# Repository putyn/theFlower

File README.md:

the flower
=========

leds, low power msp430, custom pcb shape, oshpark purple & ENIG

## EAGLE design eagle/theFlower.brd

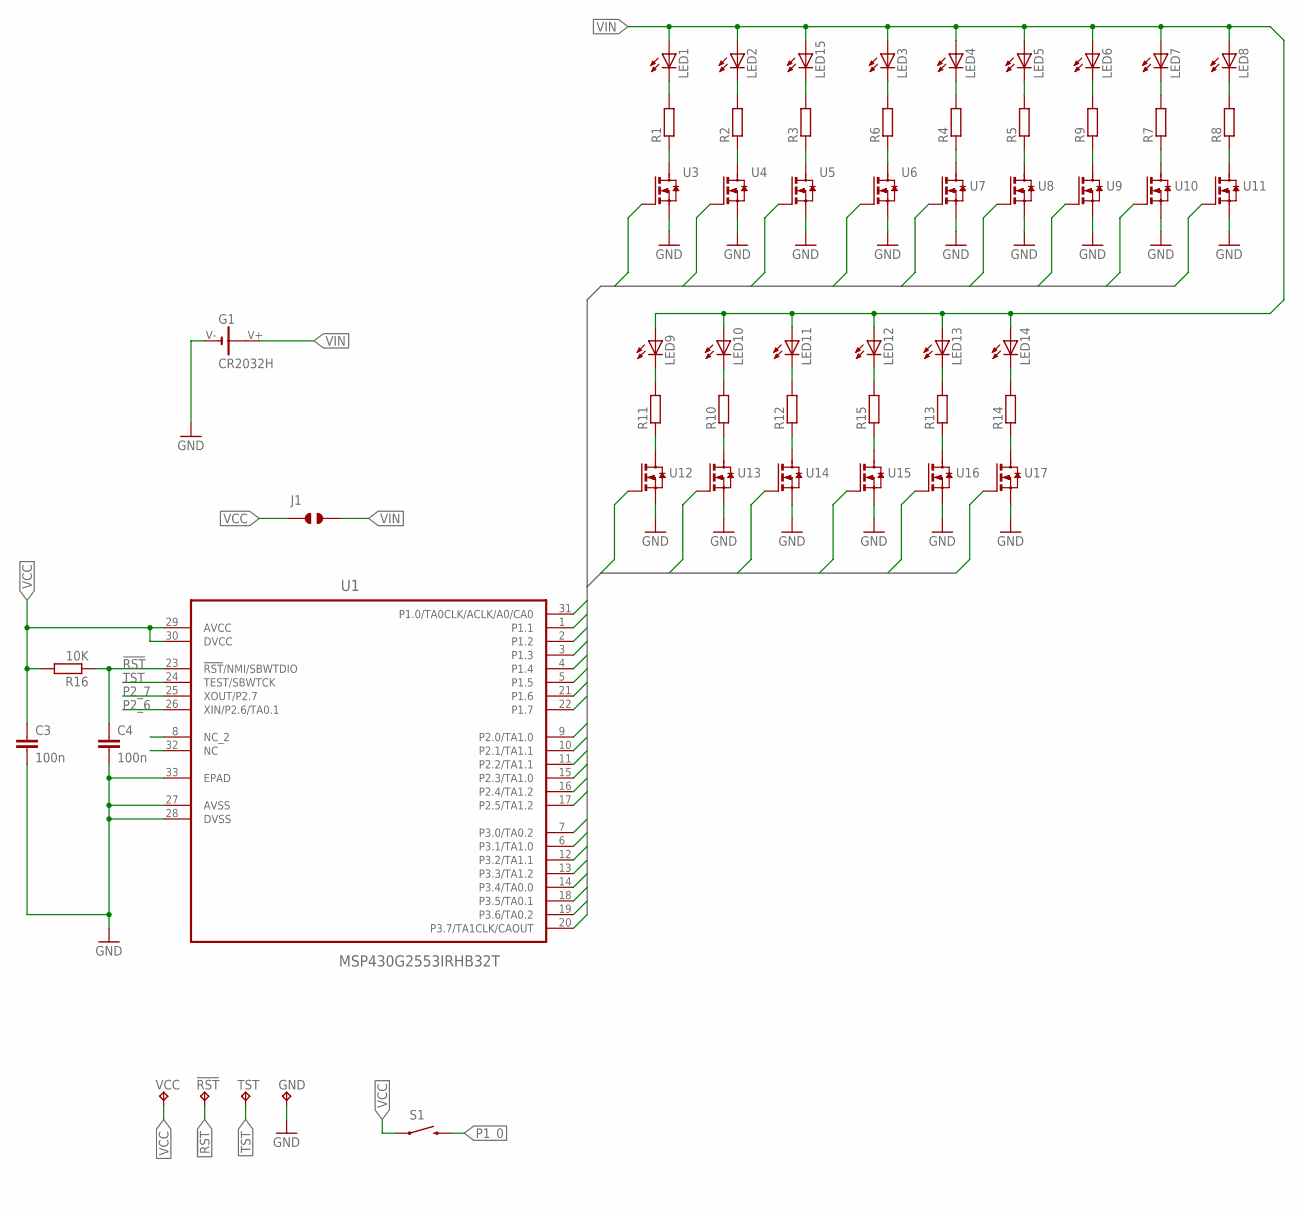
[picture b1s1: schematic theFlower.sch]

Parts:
!RST!: TPAD0.8MM_RUND; TPAD_0.8MM_RUND
C3, C4: 100n; C0603
G1: CR2032H; CH7410-2032LF
GND: TPAD0.8MM_RUND; TPAD_0.8MM_RUND
J1: JUMPER_SOLDER_1X2
LED1, LED2, LED3, LED4, LED5, LED6, LED7, LED8, LED9, LED10, LED11, LED12, LED13, LED14, LED15: LEDCHIP-LED0805; CHIP-LED0805
R1, R2, R3, R4, R5, R6, R7, R8, R9, R10, R11, R12, R13, R14, R15: R-EU_R0603; R0603
R16: 10K; R0603
S1: SWITCH-MOMENTARY-2SMD; TACTILE-SWITCH-SMD
TST: TPAD0.8MM_RUND; TPAD_0.8MM_RUND
U1: MSP430G2553IRHB32T; QFN50P500X500X100-33N
U3, U4, U5, U6, U7, U8, U9, U10, U11, U12, U13, U14, U15, U16, U17: BSS138BKW; SOT65P210X110-3N
VCC: TPAD0.8MM_RUND; TPAD_0.8MM_RUND

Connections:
!RST!: !RST!.1, C4.1, R16.1, U1.23 (!RST!/NMI/SBWTDIO)
GND: C3.2, C4.2, G1.V-, GND.1, U1.27 (AVSS), U1.28 (DVSS), U1.33 (EPAD), U3.2 (S), U4.2 (S), U5.2 (S), U6.2 (S), U7.2 (S), U8.2 (S), U9.2 (S), U10.2 (S), U11.2 (S), U12.2 (S), U13.2 (S), U14.2 (S), U15.2 (S), U16.2 (S), U17.2 (S)
unnamed: LED1.C, R1.2
unnamed: LED2.C, R2.2
unnamed: LED15.C, R3.2
unnamed: LED4.C, R4.2
unnamed: LED5.C, R5.2
unnamed: LED3.C, R6.2
unnamed: LED7.C, R7.2
unnamed: LED8.C, R8.2
unnamed: LED6.C, R9.2
unnamed: LED10.C, R10.2
unnamed: LED9.C, R11.2
unnamed: LED11.C, R12.2
unnamed: LED13.C, R13.2
unnamed: LED14.C, R14.2
unnamed: LED12.C, R15.2
unnamed: R1.1, U3.3 (D)
unnamed: R2.1, U4.3 (D)
unnamed: R3.1, U5.3 (D)
unnamed: R6.1, U6.3 (D)
unnamed: R4.1, U7.3 (D)
unnamed: R5.1, U8.3 (D)
unnamed: R9.1, U9.3 (D)
unnamed: R7.1, U10.3 (D)
unnamed: R8.1, U11.3 (D)
unnamed: R11.1, U12.3 (D)
unnamed: R10.1, U13.3 (D)
unnamed: R12.1, U14.3 (D)
unnamed: R15.1, U15.3 (D)
unnamed: R13.1, U16.3 (D)
unnamed: R14.1, U17.3 (D)
NC: U1.32 (NC)
NC_2: U1.8 (NC_2)
P1_0: S1.3 (2), U1.31 (P1.0/TA0CLK/ACLK/A0/CA0)
P1_1: U1.1 (P1.1), U5.1 (G)
P1_2: U1.2 (P1.2), U3.1 (G)
P1_3: U1.3 (P1.3), U4.1 (G)
P1_4: U1.4 (P1.4), U6.1 (G)
P1_5: U1.5 (P1.5), U7.1 (G)
P1_6: U1.21 (P1.6), U16.1 (G)
P1_7: U1.22 (P1.7), U17.1 (G)
P2_0: U1.9 (P2.0/TA1.0), U10.1 (G)
P2_1: U1.10 (P2.1/TA1.1), U11.1 (G)
P2_2: U1.11 (P2.2/TA1.1), U12.1 (G)
P2_3: U1.15 (P2.3/TA1.0)
P2_4: U1.16 (P2.4/TA1.2)
P2_5: U1.17 (P2.5/TA1.2)
P2_6: U1.26 (XIN/P2.6/TA0.1)
P2_7: U1.25 (XOUT/P2.7)
P3_0: U1.7 (P3.0/TA0.2), U9.1 (G)
P3_1: U1.6 (P3.1/TA1.0), U8.1 (G)
P3_2: U1.12 (P3.2/TA1.1), U13.1 (G)
P3_3: U1.13 (P3.3/TA1.2), U14.1 (G)
P3_4: U1.14 (P3.4/TA0.0)
P3_5: U1.18 (P3.5/TA0.1)
P3_6: U1.19 (P3.6/TA0.2)
P3_7: U1.20 (P3.7/TA1CLK/CAOUT), U15.1 (G)
TST: TST.1, U1.24 (TEST/SBWTCK)
VCC: C3.1, J1.1, R16.2, S1.1, U1.29 (AVCC), U1.30 (DVCC), VCC.1
VIN: G1.V+, J1.2, LED1.A, LED2.A, LED3.A, LED4.A, LED5.A, LED6.A, LED7.A, LED8.A, LED9.A, LED10.A, LED11.A, LED12.A, LED13.A, LED14.A, LED15.A

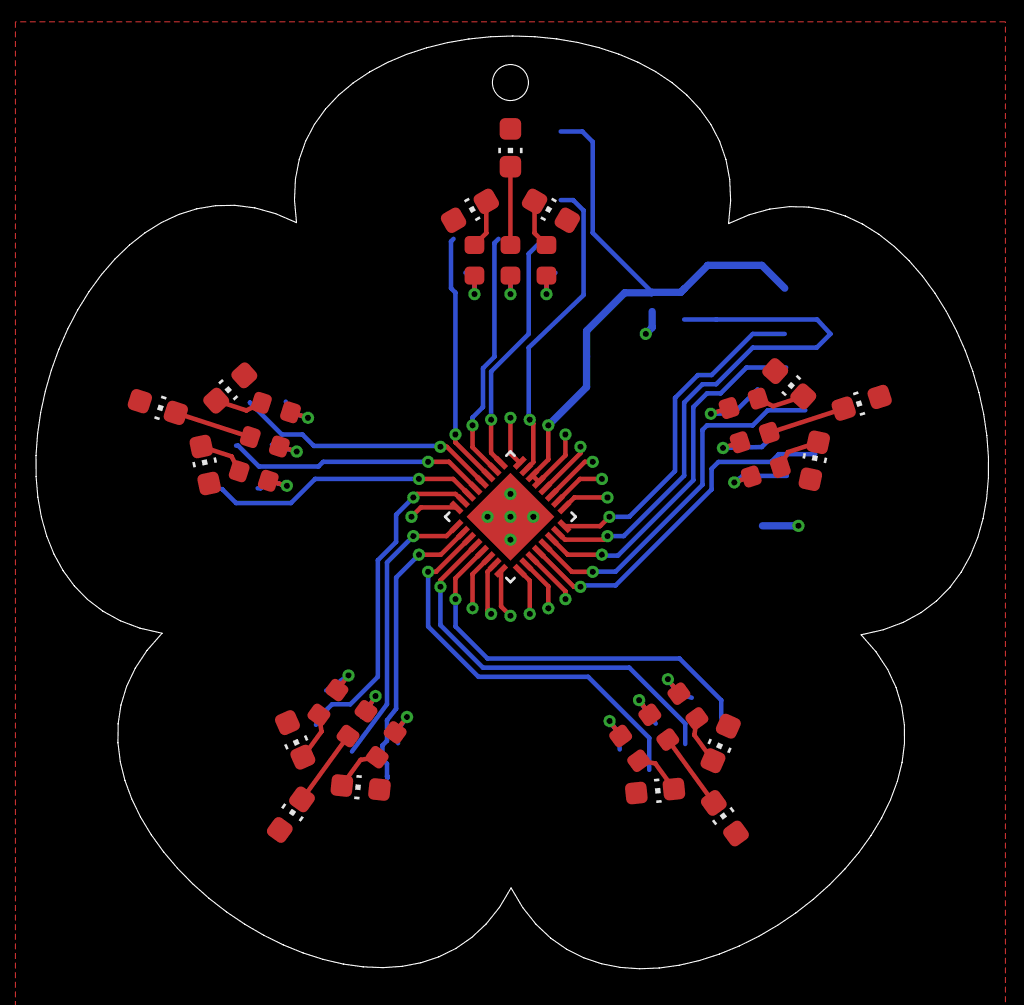
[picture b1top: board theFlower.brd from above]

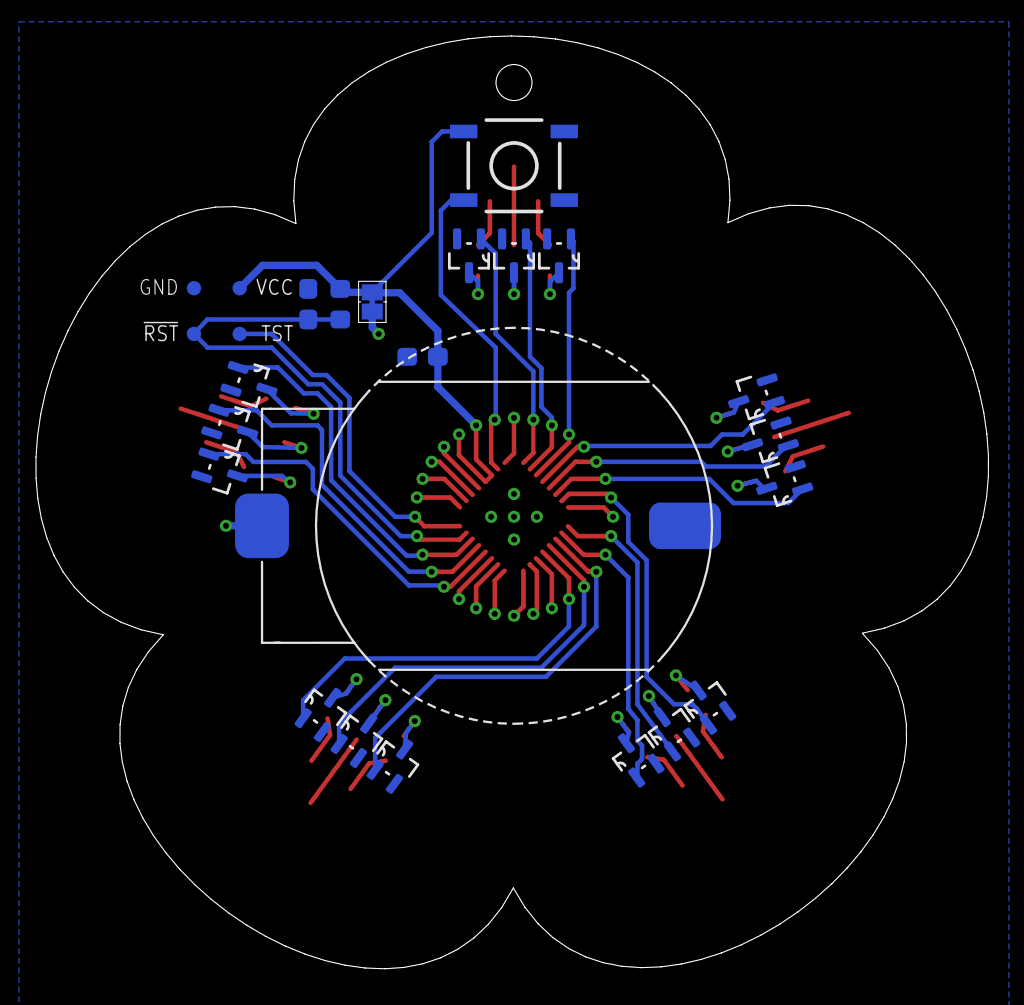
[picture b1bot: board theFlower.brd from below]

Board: 2 copper layers, 52.9 x 51.8 mm, 56 parts (25 on the bottom side), 51 nets.

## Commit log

2017-01-12 :space_invader: Added .gitattributes & .gitignore files
2017-01-12 local-repo
2017-01-12 added software
2017-01-13 readme + pics

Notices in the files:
parts and their libraries:
SparkFun-Electromechanical: Licensing: CC v3.0 Share-Alike You are welcome to use this library for commercial purposes.
